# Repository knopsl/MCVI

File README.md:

# MCVI

This is a simple MIDI to CV synth module in Kosmo format. It provides pitch and velocity CV, gate, and trigger for Note On events as well as pitch bend and modulation CV for one MIDI channel, and 1- and 4- pulse per quarter note clock outputs.

This project is adapted from [https://github.com/elkayem/midi2cv](https://github.com/elkayem/midi2cv). 

It handles a range of 88 MIDI notes, corresponding to a standard piano keyboard, using a 12 bit DAC. CV output is 0 V (for MIDI note 21, A0) to +7.25 V (MIDI note 88, C8). Note selection in case of multple keys pressed is governed by a switch selecting lowest note, highest note, or most recent note priority.

Pitch bend CV range is 0 to +1.0 V (0.5 V when centered). Velocity and modulation CV range is 0 to +4 V. Gate, trigger, and clock outputs are +5 V; trigger and clock pulse width is 20 ms.

The module is built around an Arduino Nano. The sketch uses the standard MIDI and SPI libraries.

## Documentation
* [Build notes](Docs/build_notes.md) 
* [Schematic](Docs/MCVI.pdf)
* [BOM](Docs/MCVI_bom.pdf)

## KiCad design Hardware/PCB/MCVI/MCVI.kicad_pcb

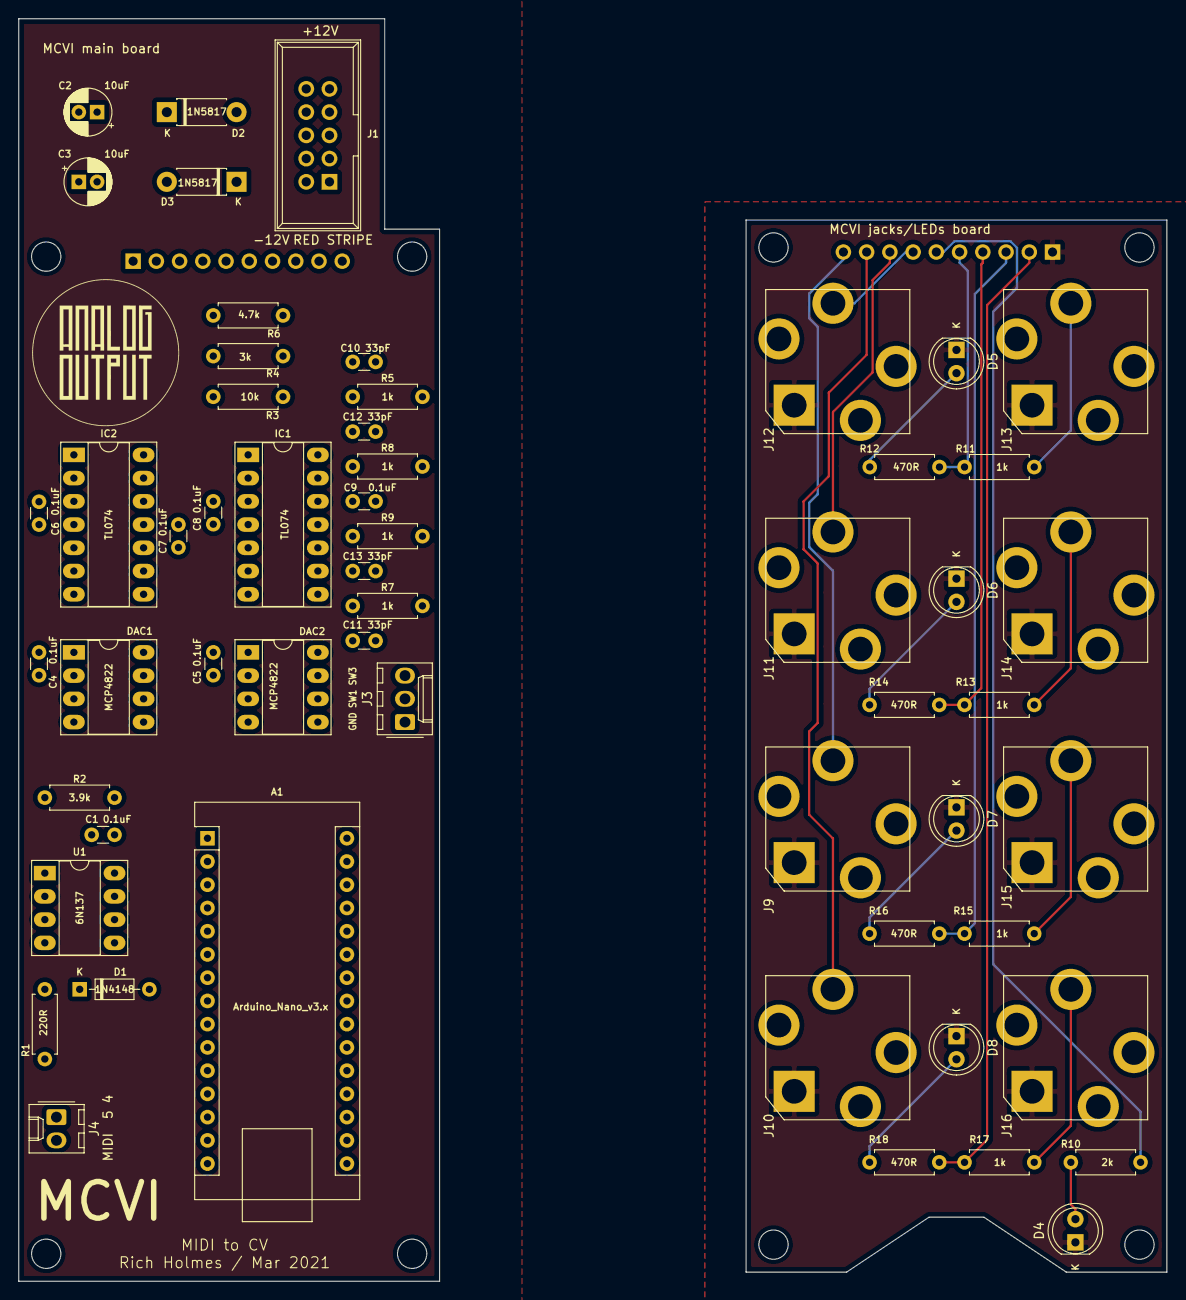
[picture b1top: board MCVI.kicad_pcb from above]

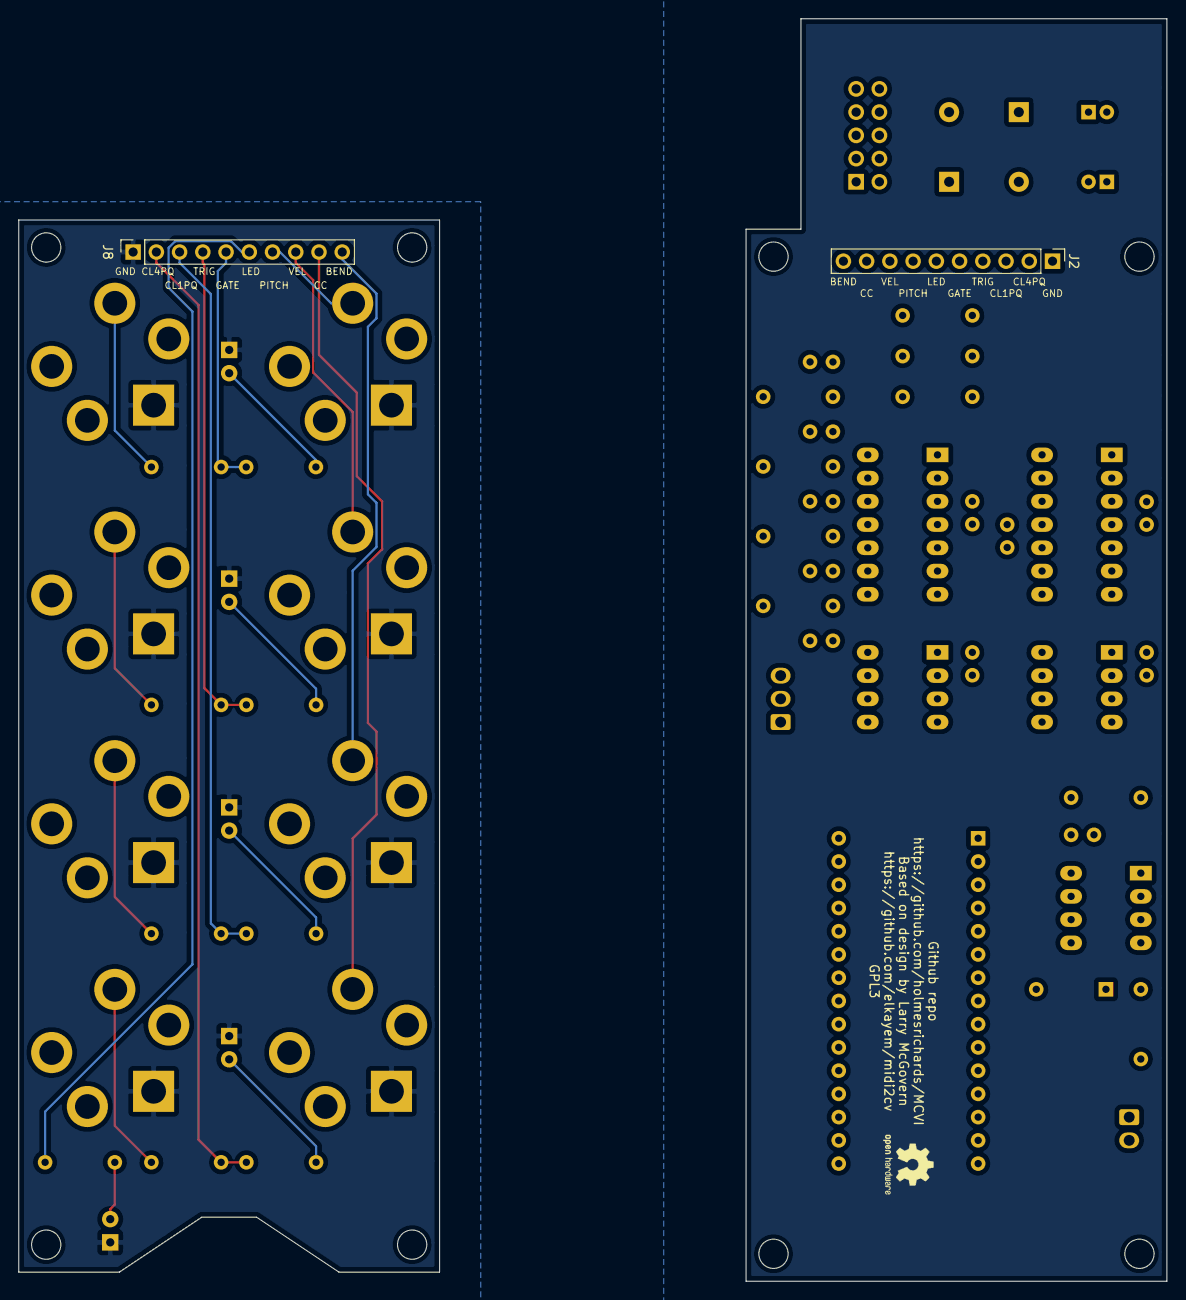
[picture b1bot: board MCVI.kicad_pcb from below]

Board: 2 copper layers, 125.5 x 138.0 mm, 69 parts (3 on the bottom side), 19 nets.

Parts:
A1: Arduino_Nano_v3.x; Arduino_Nano
C1, C4, C5, C6, C7, C8, C9: 0.1uF; C_Disc_D3.0mm_W1.6mm_P2.50mm
C2, C3: 10uF; CP_Radial_D5.0mm_P2.00mm
C10, C11, C12, C13: 33pF; C_Disc_D3.0mm_W1.6mm_P2.50mm
D1: 1N4148; D_DO-35_SOD27_P7.62mm_Horizontal
D2, D3: 1N5817; D_DO-41_SOD81_P7.62mm_Horizontal
D4: Red LED; LED_D5.0mm
D5, D6, D7, D8: Green LED; LED_D5.0mm
DAC1, DAC2: MCP4822; DIP-8_W7.62mm_Socket_LongPads
GRAF1: AO logo; analogoutput
GRAF2: OSHW logo; OSHW-Logo2_7.3x6mm_SilkScreen
GRAF3: Panel holes; MCVI_panel_holes
H1, H2, H3, H4, H5, H6, H7, H8: MountingHole; MountingHole_3.2mm_M3
IC1, IC2: TL074; DIP-14_W7.62mm_Socket_LongPads
J1: Synth_power_2x5; Power_Header
J2: 10 pin header; PinHeader_1x10_P2.54mm_Vertical
J3: 3 pin Molex header; Molex_KK-254_AE-6410-03A_1x03_P2.54mm_Vertical
J4: 2 pin Molex header; Molex_KK-254_AE-6410-02A_1x02_P2.54mm_Vertical
J8: 10 pin socket; PinSocket_1x10_P2.54mm_Vertical
J9, J10, J11, J12, J13, J14, J15, J16: AudioJack2; Jack_6.35mm_PJ_629HAN
R1: 220R; R_Axial_DIN0207_L6.3mm_D2.5mm_P7.62mm_Horizontal
R2: 3.9k; R_Axial_DIN0207_L6.3mm_D2.5mm_P7.62mm_Horizontal
R3: 10k; R_Axial_DIN0207_L6.3mm_D2.5mm_P7.62mm_Horizontal
R4: 3k; R_Axial_DIN0207_L6.3mm_D2.5mm_P7.62mm_Horizontal
R5, R7, R8, R9, R11, R13, R15, R17: 1k; R_Axial_DIN0207_L6.3mm_D2.5mm_P7.62mm_Horizontal
R6: 4.7k; R_Axial_DIN0207_L6.3mm_D2.5mm_P7.62mm_Horizontal
R10: 2k; R_Axial_DIN0207_L6.3mm_D2.5mm_P7.62mm_Horizontal
R12, R14, R16, R18: 470R; R_Axial_DIN0207_L6.3mm_D2.5mm_P7.62mm_Horizontal
U1: 6N137; DIP-8_W7.62mm_Socket_LongPads

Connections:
/Panel components/CLOCK_1PQ: J15.T, R15.1
/Panel components/CLOCK_1PQ_C: J8.3, R15.2, R16.2
/Panel components/CLOCK_4PQ: J16.T, R17.1
/Panel components/CLOCK_4PQ_C: J8.2, R17.2, R18.2
/Panel components/CONTROL: J8.9, J10.T
/Panel components/GATE: J13.T, R11.1
/Panel components/GATE_C: J8.5, R11.2, R12.2
/Panel components/MIDI_LED_C: J8.6, R10.2
/Panel components/NOTE: J8.7, J12.T
/Panel components/PITCH_BEND: J8.10, J9.T
/Panel components/TRIGGER: J14.T, R13.1
/Panel components/TRIGGER_C: J8.4, R13.2, R14.2
/Panel components/VELOCITY: J8.8, J11.T
GND1: D4.1, D5.1, D6.1, D7.1, D8.1, J8.1, J9.S, J10.S, J11.S, J12.S, J13.S, J14.S, J15.S, J16.S
unnamed: D4.2, R10.1
unnamed: D5.2, R12.1
unnamed: D6.2, R14.1
unnamed: D7.2, R16.1
unnamed: D8.2, R18.1

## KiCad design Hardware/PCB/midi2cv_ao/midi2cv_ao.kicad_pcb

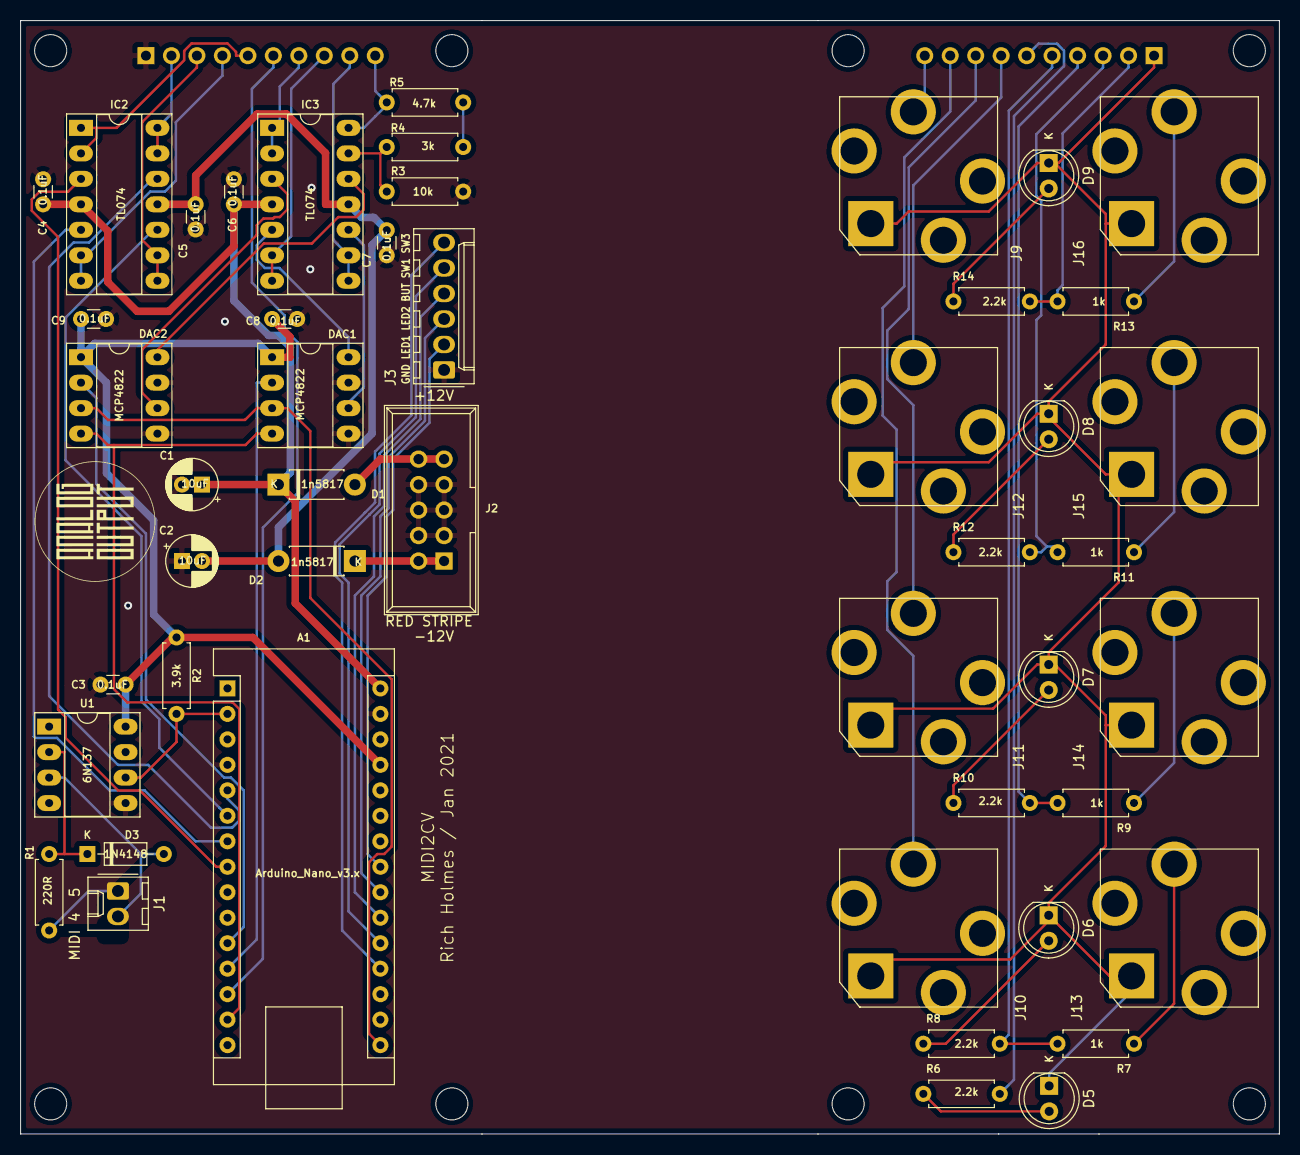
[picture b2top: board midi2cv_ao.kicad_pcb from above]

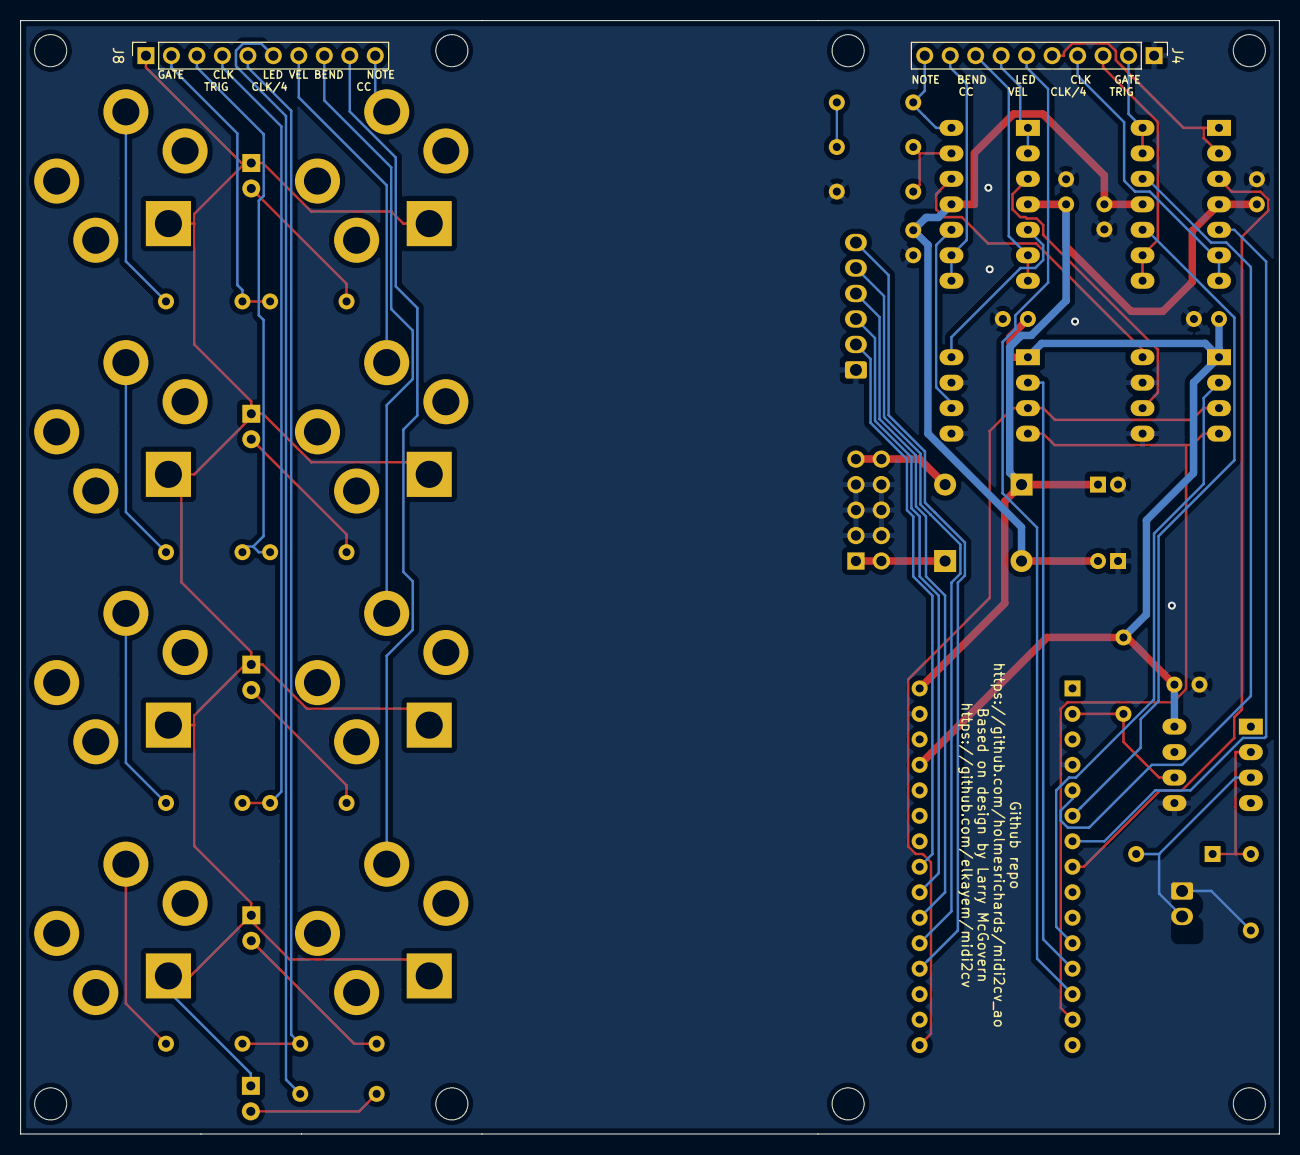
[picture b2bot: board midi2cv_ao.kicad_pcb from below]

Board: 2 copper layers, 125.5 x 111.0 mm, 50 parts (2 on the bottom side), 57 nets.

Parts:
A1: Arduino_Nano_v3.x; Arduino_Nano
C1, C2: 10uF; CP_Radial_D5.0mm_P2.00mm
C3, C4, C5, C6, C7, C8, C9: 0.1uF; C_Disc_D3.0mm_W1.6mm_P2.50mm
D1, D2: 1n5817; D_DO-41_SOD81_P7.62mm_Horizontal
D3: 1N4148; D_DO-35_SOD27_P7.62mm_Horizontal
D5, D6, D7, D8, D9: LED; LED_D5.0mm
DAC1, DAC2: MCP4822; DIP-8_W7.62mm_Socket_LongPads
IC2, IC3: TL074; DIP-14_W7.62mm_Socket_LongPads
J1: Conn_01x02; Molex_KK-254_AE-6410-02A_1x02_P2.54mm_Vertical
J2: Synth_power_2x5; Power_Header
J3: Conn_01x06; Molex_KK-254_AE-6410-06A_1x06_P2.54mm_Vertical
J4: Conn_01x10; PinHeader_1x10_P2.54mm_Vertical
J8: Conn_01x10; PinSocket_1x10_P2.54mm_Vertical
J9, J10, J11, J12, J13, J14, J15, J16: AudioJack2; Jack_6.35mm_PJ_629HAN
R1: 220R; R_Axial_DIN0207_L6.3mm_D2.5mm_P7.62mm_Horizontal
R2: 3.9k; R_Axial_DIN0207_L6.3mm_D2.5mm_P7.62mm_Horizontal
R3: 10k; R_Axial_DIN0207_L6.3mm_D2.5mm_P7.62mm_Horizontal
R4: 3k; R_Axial_DIN0207_L6.3mm_D2.5mm_P7.62mm_Horizontal
R5: 4.7k; R_Axial_DIN0207_L6.3mm_D2.5mm_P7.62mm_Horizontal
R6, R8, R10, R12, R14: 2.2k; R_Axial_DIN0207_L6.3mm_D2.5mm_P7.62mm_Horizontal
R7, R9, R11, R13: 1k; R_Axial_DIN0207_L6.3mm_D2.5mm_P7.62mm_Horizontal
U1: 6N137; DIP-8_W7.62mm_Socket_LongPads

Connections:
+5V: A1.27, C3.2, C8.1, C9.1, DAC1.1, DAC2.1, R2.1, U1.8
+12V: A1.30, C1.1, C4.1, C6.1, D1.1, IC2.4, IC3.4
-12V: C2.2, C5.2, C7.2, D2.2, IC2.11, IC3.11
/BUT: A1.21, J3.4
/CLOCK_4_A: IC2.1, IC2.2, J4.5
/CLOCK_4_B: A1.8, IC2.3
/CLOCK_A: IC2.6, IC2.7, J4.4
/CLOCK_B: A1.7, IC2.5
/CONTROL_A: IC3.8, IC3.9, J4.9
/DAC1_SEL: A1.11, DAC2.2
/DAC2_SEL: A1.12, DAC1.2
/GATE_A: IC2.13, IC2.14, J4.2
/GATE_B: A1.5, IC2.12
/MIDIPIN4: J1.1, R1.2
/MIDIPIN5: D3.2, J1.2, U1.3
/MIDI_LED_A: A1.13, J4.6
/NOTE_A: IC3.14, J4.10, R5.1
/PITCH_BEND_A: IC3.6, IC3.7, J4.8
/PROG_LED1: A1.22, J3.3
/PROG_LED2: A1.23, J3.2
/Panel components/CLOCK: J14.T, R9.1
/Panel components/CLOCK_4: J13.T, R7.1
/Panel components/CONTROL: J8.9, J10.T
/Panel components/GATE: J16.T, R13.1
/Panel components/NOTE: J8.10, J9.T
/Panel components/PITCH_BEND: J8.8, J11.T
/Panel components/TRIGGER: J15.T, R11.1
/Panel components/VELOCITY: J8.7, J12.T
/RX0: A1.2, R2.2, U1.6
/SCK: A1.16, DAC1.3, DAC2.3
/SDI: A1.14, DAC1.4, DAC2.4
/SW1: A1.20, J3.5
/SW3: A1.19, J3.6
/TRIGGER_A: IC2.8, IC2.9, J4.3
/TRIGGER_B: A1.6, IC2.10
/VELOCITY_A: IC3.1, IC3.2, J4.7
GND: A1.4, A1.29, C1.2, C2.1, C3.1, C4.2, C5.1, C6.2, C7.1, C8.2, C9.2, DAC1.5, DAC1.7, DAC2.5, DAC2.7, J2.3, J2.4, J2.5, J2.6, J2.7, J2.8, J3.1, J4.1, R3.1, U1.5
GND1: D5.1, D6.1, D7.1, D8.1, D9.1, J8.1, J9.S, J10.S, J11.S, J12.S, J13.S, J14.S, J15.S, J16.S
unnamed: D1.2, J2.9, J2.10
unnamed: D2.1, J2.1, J2.2
unnamed: D3.1, R1.1, U1.2
unnamed: D5.2, R6.1
unnamed: D6.2, R8.1
unnamed: D7.2, R10.1
unnamed: D8.2, R12.1
unnamed: D9.2, R14.1
unnamed: DAC1.6, IC3.10
unnamed: DAC1.8, IC3.5
unnamed: DAC2.6, IC3.3
unnamed: DAC2.8, IC3.12
unnamed: IC3.13, R3.2, R4.2
unnamed: J8.2, R13.2, R14.2
unnamed: J8.3, R11.2, R12.2
unnamed: J8.4, R9.2, R10.2
unnamed: J8.5, R7.2, R8.2
unnamed: J8.6, R6.2
unnamed: R4.1, R5.2

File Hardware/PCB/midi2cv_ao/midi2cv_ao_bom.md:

# midi2cv_ao.sch BOM

Wed 24 Feb 2021 09:03:12 PM EST

Generated from schematic by Eeschema 5.1.9-73d0e3b20d~88~ubuntu20.04.1

**Component Count:** 56

| Value | Qty | Part | Description | Vendor |
| ----- | --- | ---- | ----------- | ------ |
| A1 | 1 | Arduino_Nano_v3.x | Arduino Nano v3.x |  |
| C1, C2 | 2 | 10uF | Polarized capacitor |  |
| C3, C4, C5, C6, C7, C8, C9 | 7 | 0.1uF | Unpolarized capacitor |  |
| D1, D2 | 2 | 1n5817 | Schottky diode |  |
| D3 | 1 | 1N4148 | 100V 0.15A standard switching diode, DO-35 |  |
| D4 | 1 | LED_Dual_ACA | Dual LED, common cathode on pin 2 |  |
| D5, D6, D7, D8, D9 | 5 | LED | Light emitting diode |  |
| DAC1, DAC2 | 2 | MCP4822 | 2-Channel 12-Bit D/A Converters with SPI Interface and Internal Reference (2.048V) |  |
| IC2, IC3 | 2 | TL074 | Quad Low-Noise JFET-Input Operational Amplifiers, DIP-14/SOIC-14 |  |
| J1 | 1 | Conn_01x02 | Generic connector, single row, 01x02, script generated (kicad-library-utils/schlib/autogen/connector/) |  |
| J2 | 1 | Synth_power_2x5 | 2x5 shrouded 2.54mm pin header |  |
| J3, J7 | 2 | Conn_01x06 | Generic connector, single row, 01x06, script generated (kicad-library-utils/schlib/autogen/connector/) |  |
| J4 | 1 | Conn_01x10 | Generic connector, single row, 01x10, script generated (kicad-library-utils/schlib/autogen/connector/) |  |
| J5 | 1 | MIDIJACK | 5-pin DIN connector (5-pin DIN-5 stereo) |  |
| J6 | 1 | Conn_01x02 | Generic connector, single row, 01x02, script generated (kicad-library-utils/schlib/autogen/connector/) |  |
| J8 | 1 | Conn_01x10 | Generic connector, single row, 01x10, script generated (kicad-library-utils/schlib/autogen/connector/) |  |
| J9, J10, J11, J12, J13, J14, J15, J16 | 8 | AudioJack2 | Audio Jack, 2 Poles (Mono / TS) |  |
| R1 | 1 | 220R | Resistor |  |
| R2 | 1 | 3.9k | Resistor |  |
| R3 | 1 | 10k | Resistor |  |
| R4 | 1 | 3k | Resistor |  |
| R5 | 1 | 4.7k | Resistor |  |
| R6, R8, R10, R12, R14 | 5 | 2.2k | Resistor |  |
| R7, R9, R11, R13 | 4 | 1k | Resistor |  |
| SW1 | 1 | SW_Push | Push button switch, generic, two pins |  |
| SW2 | 1 | SW_SPDT | Switch, single pole double throw |  |
| U1 | 1 | 6N137 | Single High Speed LSTTL/TTL Compatible Optocoupler with enable, dV/dt 1000/us, VCM 10, max 7V VCC, DIP-8 |  |

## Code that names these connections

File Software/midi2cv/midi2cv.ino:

/*
  MIDI2CV
  Copyright (C) 2017  Larry McGovern

  This program is free software: you can redistribute it and/or modify
  it under the terms of the GNU General Public License as published by
  the Free Software Foundation, either version 3 of the License, or
  (at your option) any later version.

  This program is distributed in the hope that it will be useful,
  but WITHOUT ANY WARRANTY; without even the implied warranty of
  MERCHANTABILITY or FITNESS FOR A PARTICULAR PURPOSE.  See the
  GNU General Public License <http://www.gnu.org/licenses/> for more details.
*/

/*
  Version by Rich Holmes:
  * Some reformatting and reordering
  * Add 4 per quarter note clock
  * Listen only to selected channel
  * Ignore CC if not mod wheel

  License: GPL3 as above.
*/

#include <MIDI.h>
#include <SPI.h>

// Note priority is set by pins A0 and A2
// Highest note priority: A0 and A2 high (open)
// Lowest note priority:  A0 low (ground), A2 high (open)
// Last note priority:    A2 low (ground)

#define NP_SEL1 A0  // Note priority is set by pins A0 and A2
#define NP_SEL2 A2

#define GATE  2
#define TRIG  3
#define CLOCK_1PQ 4
#define CLOCK_4PQ 5
#define DAC1  8
#define DAC2  9
#define MIDILED 10

#define CHANNEL 1  // Use only this channel

MIDI_CREATE_DEFAULT_INSTANCE();

void setup()
{
  pinMode(NP_SEL1, INPUT_PULLUP);
  pinMode(NP_SEL2, INPUT_PULLUP);

  pinMode(GATE, OUTPUT);
  pinMode(TRIG, OUTPUT);
  pinMode(CLOCK_1PQ, OUTPUT);
  pinMode(CLOCK_4PQ, OUTPUT);
  pinMode(DAC1, OUTPUT);
  pinMode(DAC2, OUTPUT);
  pinMode(MIDILED, OUTPUT);
  digitalWrite(GATE, LOW);
  digitalWrite(TRIG, LOW);
  digitalWrite(CLOCK_1PQ, LOW);
  digitalWrite(CLOCK_4PQ, LOW);
  digitalWrite(DAC1, HIGH);
  digitalWrite(DAC2, HIGH);
  digitalWrite(MIDILED, LOW);

  SPI.begin();

  MIDI.begin(CHANNEL);


  // Set initial pitch bend voltage to 0.5V (mid point).  With Gain = 1X, this is 1023
  // Other DAC outputs will come up as 0V, so don't need to be initialized
  setVoltage(DAC2, 0, 0, 1023);
}

bool notes[88] = {0};
int8_t noteOrder[20] = {0}, orderIndx = {0};
unsigned long trigTimer = 0;

void loop()
{
  int type, noteMsg, velocity, d1, d2;
  static unsigned long clock_timer = 0, clock_timeout = 0;
  static unsigned int clock_count = 0;
  static unsigned long midiled_timer = 0;
  bool S1, S2;

  if ((midiled_timer > 0) && (millis() - midiled_timer > 20))
    {
      digitalWrite(MIDILED, LOW); // Set MIDI LED low after 20 msec
      midiled_timer = 0;
    }
    
  if ((trigTimer > 0) && (millis() - trigTimer > 20))
    {
      digitalWrite(TRIG, LOW); // Set trigger low after 20 msec
      trigTimer = 0;
    }

  if ((clock_timer > 0) && (millis() - clock_timer > 20))
    {
      digitalWrite(CLOCK_1PQ, LOW); // Set clock pulse low after 20 msec
      digitalWrite(CLOCK_4PQ, LOW); // Set clock pulse low after 20 msec
      clock_timer = 0;
    }

  if (MIDI.read())
    {
      digitalWrite(MIDILED, HIGH);
      midiled_timer = millis();
      byte type = MIDI.getType();
      switch (type)
	{
	case midi::ActiveSensing:
	  break;

	case midi::Clock:
	  if (millis() > clock_timeout + 300) clock_count = 0; // Prevents Clock from starting in between quarter notes after clock is restarted!
	  clock_timeout = millis();

	  // MIDI timing clock sends 24 pulses per quarter note.
	  // Sent CLOCK_1PQ pulse only once every 24 pulses
	  // Sent CLOCK_4PQ pulse only once every 6 pulses
	  
	  if (clock_count == 0)
	    digitalWrite(CLOCK_1PQ, HIGH); // Start CLOCK_1PQ pulse
	  if (clock_count == 0 || clock_count == 6
	      || clock_count == 12 || clock_count == 18)
	    {
	      digitalWrite(CLOCK_4PQ, HIGH); // Start CLOCK_4PQ pulse
	      clock_timer = millis();
	    }
	  clock_count++;
	  if (clock_count == 24)
	    clock_count = 0;
	  break;

	case midi::NoteOn:
	case midi::NoteOff:
	  noteMsg = MIDI.getData1() - 21; // A0 = 21, Top Note = 108

	  if ((noteMsg < 0) || (noteMsg > 87)) 
	    break; // Only 88 notes of keyboard are supported

	  if (type == midi::NoteOn) 
	    velocity = MIDI.getData2();
	  else 
	    velocity  = 0;

	  if (velocity == 0)
	    notes[noteMsg] = false;
	  else
	    {
	      notes[noteMsg] = true;
	      // velocity range from 0 to 4095 mV. Left shift d2 by 5
	      // to scale from 0 to 4095, and choose gain = 2X
	      setVoltage(DAC1, 1, 1, velocity << 5); // DAC1, channel 1, gain = 2X
	    }

	  // Pins NP_SEL1 and NP_SEL2 indictate note priority
	  S1 = digitalRead(NP_SEL1);
	  S2 = digitalRead(NP_SEL2);

	  if (S1 && S2)
	    commandTopNote(); // Highest note priority
	  else if (!S1 && S2)
	    commandBottomNote(); // Lowest note priority
	  else
	    {
	      // Last note priority
	      if (notes[noteMsg])
		{
		  // If note is on and using last note priority, add
		  // to ordered list
		  orderIndx = (orderIndx + 1) % 20;
		  noteOrder[orderIndx] = noteMsg;
		}
	      commandLastNote();
	    }
	  break;

	case midi::PitchBend:
	  // Pitch bend output from 0 to 1023 mV.  Left shift d2 by 4
	  // to scale from 0 to 2047.  With DAC gain = 1X, this will
	  // yield a range from 0 to 1023 mV.
	  d2 = MIDI.getData2(); // d2 from 0 to 127, mid point = 64
	  setVoltage(DAC2, 0, 0, d2 << 4); // DAC2, channel 0, gain = 1X
	  break;

	case midi::ControlChange:
	  d1 = MIDI.getData1();
	  if (d1 != 1) // CC 1 (mod wheel) only
	    break;
	  
	  // CC range from 0 to 4095 mV Left shift d2 by 5 to scale
	  // from 0 to 4095, and choose gain = 2X
	  d2 = MIDI.getData2(); // From 0 to 127
	  setVoltage(DAC2, 1, 1, d2 << 5); // DAC2, channel 1, gain = 2X
	  break;

	default:
	  break;
	}
    }
}

void commandTopNote()
{
  int topNote = 0;
  bool noteActive = false;

  for (int i = 0; i < 88; i++)
    {
      if (notes[i])
	{
	  topNote = i;
	  noteActive = true;
	}
    }

  if (noteActive)
    commandNote(topNote);
  else // All notes are off, turn off gate
    digitalWrite(GATE, LOW);
}

void commandBottomNote()
{
  int bottomNote = 0;
  bool noteActive = false;

  for (int i = 87; i >= 0; i--)
    {
      if (notes[i])
	{
	  bottomNote = i;
	  noteActive = true;
	}
    }

  if (noteActive)
    commandNote(bottomNote);
  else // All notes are off, turn off gate
    digitalWrite(GATE, LOW);
}

void commandLastNote()
{

  int8_t noteIndx;

  for (int i = 0; i < 20; i++)
    {
      noteIndx = noteOrder[mod(orderIndx - i, 20)];
      if (notes[noteIndx])
	{
	  commandNote(noteIndx);
	  return;
	}
    }
  digitalWrite(GATE, LOW); // All notes are off
}

// Rescale 88 notes to 4096 mV:
//    noteMsg = 0 -> 0 mV
//    noteMsg = 87 -> 4096 mV

// DAC output will be (4095/87) = 47.069 mV per note, and 564.9655 mV
// per octave. Note that DAC output will need to be amplified by 1.77X
// for the standard 1V/octave.

#define NOTE_SF 47.069f // This value can be tuned if CV output isn't exactly 1V/octave

void commandNote(int noteMsg)
{
  digitalWrite(GATE, HIGH);
  digitalWrite(TRIG, HIGH);
  trigTimer = millis();

  unsigned int mV = (unsigned int) ((float) noteMsg * NOTE_SF + 0.5);
  setVoltage(DAC1, 0, 1, mV);  // DAC1, channel 0, gain = 2X
}

// setVoltage -- Set DAC voltage output

// dacpin: chip select pin for DAC.  Note and velocity on DAC1, pitch
// bend and CC on DAC2
//
// channel: 0 (A) or 1 (B).  Note and pitch bend on 0, velocity and CC on 2.
//
// gain: 0 = 1X, 1 = 2X.
//
// mV: integer 0 to 4095.  If gain is 1X, mV is in units of half mV
// (i.e., 0 to 2048 mV).
//
// If gain is 2X, mV is in units of mV.

void setVoltage(int dacpin, bool channel, bool gain, unsigned int mV)
{
  unsigned int command = channel ? 0x9000 : 0x1000;

  command |= gain ? 0x0000 : 0x2000;
  command |= (mV & 0x0FFF);

  SPI.beginTransaction(SPISettings(8000000, MSBFIRST, SPI_MODE0));
  digitalWrite(dacpin, LOW);
  SPI.transfer(command >> 8);
  SPI.transfer(command & 0xFF);
  digitalWrite(dacpin, HIGH);
  SPI.endTransaction();
}

int mod(int a, int b)
{
  int r = a % b;
  return r < 0 ? r + b : r;
}

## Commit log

2020-10-29 Initial version
2020-10-29 Fix image links
2020-10-29 Add Teensy symbol/footprint; change output gain stages
2020-10-30 Revert some changes (save for a later version)
2020-11-21 General updates
2021-01-02 Add buffers to digital outputs; change optoisolator
2021-01-02 Jumper for hard/soft serial select
2021-01-17 Include lib table files; backlogged changes
2021-01-23 Notes on voltage range offsets
2021-02-19 Footprints updated
2021-02-19 Add freerouting files to .gitignore
2021-02-19 New routing
2021-02-25 Changed optoisolator, new layout
2021-02-28 Rename project
2021-03-04 Readme updates, button and bicolor LED will probably be omitted
2021-03-05 Schem PDF
2021-03-05 Add 4pq clock, ignore non channel 1, ignore CC other than mod wheel
2021-03-05 Some text revisions
2021-03-05 Listen only to selected channel
2021-03-06 Added in-loop series resistors and feedback capacitors on gate outputs.
2021-03-06 Add MIDI LED to sketch
2021-03-06 Rename sketch
2021-03-06 Get rid of button and bicolor LED; reduce LED resistor values; SW1 to A2; cleanup
2021-03-06 Schematics cleanup
2021-03-06 New PCB layout
2021-03-06 New PCB Gerbers; panel design
2021-03-07 Schematics tweaks, BOM
2021-04-01 Final revisions before fabrication
2021-04-01 Gerbers, docs updates
2021-04-10 BOM updates
2021-04-16 Documentation updates
2021-05-04 Ignore my version
2021-05-04 Calibration notes
2021-05-04 Truncate high value, not mask
2021-05-04 Note on selecting DACs for performance
2021-08-07 Kosmo_panel lib update
